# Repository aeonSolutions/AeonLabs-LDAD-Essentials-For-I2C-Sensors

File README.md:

[Main Catalogue](https://github.com/aeonSolutions/PCB-Prototyping-Catalogue) >> 
[Construction Industry](https://github.com/aeonSolutions/PCB-Prototyping-Catalogue/tree/main/Construction%20Industry)  >>  Smart Technologies for Building Smart Network Connectivity

<p align="right">
 <a href="https://github-com.translate.goog/aeonSolutions/PCB-Prototyping-Catalogue/tree/main?_x_tr_sl=en&_x_tr_tl=pt&_x_tr_hl=en&_x_tr_pto=wapp">Change Language</a> <br>
Last update: 01-12-2023
</p>

# AeonLabs LDAD Essentials For I2C Sensors
This repo contains the KiCad files for the LDAD Essentials features up to  6 I2C sensor connections has WIFI and BLE connectivity and is powered by a 4.2v Lipo Battery.
This PCB was made to Fit a [Legrand Aftakdoos Leeq](https://www.google.com/search?q=Legrand+Aftakdoos+leeq&newwindow=1&client=opera&sxsrf=APq-WBudoCNXlyJkT8RVjwlvQol-xiGYpA%3A1650729585719&ei=cSJkYqmqK_GAi-gPo-ey4AQ&ved=0ahUKEwjpps70xqr3AhVxwAIHHaOzDEwQ4dUDCA0&uact=5&oq=Legrand+Aftakdoos+leeq&gs_lcp=Cgdnd3Mtd2l6EAMyBQghEKABMgUIIRCgATIFCCEQoAE6BwgAEEcQsAM6BggAEBYQHkoECEEYAEoECEYYAFDhBViiD2DMEGgBcAF4AIABpgGIAfkDkgEDMC40mAEAoAEByAEIwAEB&sclient=gws-wiz) 89x43mm waterproof enclosure.

*Don't forget to LIKE , SHARE and subscribe the free whatsApp group* and if you liked this PCB consider buying me a cup of coffee. Links below.

### Status
  revision 1.0 tested and working

If you already tested this PCB send me a message. Thank you

## Revisions
- revision 1.0
  
## Download options
Download this repository if you need the KiCad Files or, download the Gerber files in the release section of this repository

## Liked it ? Get a Free PCB for yourself
Send me your Device or hardware and i will design a custom PCB for it. Free of charge. Contact-me on WhatsApp or email for more info. 

## Q&A WhatsApp Group
If you have any Questions or simply  like this kind of projects and want to stay updated with the latest research ideas and prototypes during the day and week, join the WhatsApp Group
[A.I. Things](https://chat.whatsapp.com/FkNC7u83kuy2QRA5sqjBVg)

## Fully assembled PCB
Alternatively, and if you do not want to build a PCB by yourself and like to buy one:

The price starts at 30eur plus postage fees.
(I will also deliver the assembled PCB with all the components in place at a fair aditonal cost).

#### Be supportive of my dedication and work towards technology education and buy me a coffee. Link below.

## PCB Parts list
- DC2DC converter HX4002B x2 : https://s.click.aliexpress.com/e/_Ak7IPx
- Capacitor 100nF SMD 1206 : https://s.click.aliexpress.com/e/_AVdmzr
- Capacitor 2.2uF SMD 1206 : https://s.click.aliexpress.com/e/_AVdmzr
- Resistor SMD 1206 330R x3 : https://s.click.aliexpress.com/e/_A7OXrR
- ESP32 WROOM32 x1 : https://s.click.aliexpress.com/e/_AF7N6l
- KF350 Screw pitch 3.5mm Straight 3 Pin pcb terminal block : https://s.click.aliexpress.com/e/_AChDnp

- This PCB connects with the any I2C compatible sensor such as the SHT3x, SG30, etc :  https://s.click.aliexpress.com/e/_A1piJN

## PCB Enclosure
The enclosure for this PCB can be bought online by searching for "[Legrand Aftakdoos Leeq](https://www.google.com/search?q=Legrand+Aftakdoos+leeq&newwindow=1&client=opera&sxsrf=APq-WBudoCNXlyJkT8RVjwlvQol-xiGYpA%3A1650729585719&ei=cSJkYqmqK_GAi-gPo-ey4AQ&ved=0ahUKEwjpps70xqr3AhVxwAIHHaOzDEwQ4dUDCA0&uact=5&oq=Legrand+Aftakdoos+leeq&gs_lcp=Cgdnd3Mtd2l6EAMyBQghEKABMgUIIRCgATIFCCEQoAE6BwgAEEcQsAM6BggAEBYQHkoECEEYAEoECEYYAFDhBViiD2DMEGgBcAF4AIABpgGIAfkDkgEDMC40mAEAoAEByAEIwAEB&sclient=gws-wiz)".

## Firmware Download 
one can use the PCB in the repository [AeonLabs-MCU-Burner-USB-to-UART-TTL](https://github.com/aeonSolutions/AeonLabs-MCU-Burner-USB-to-UART-TTL) to program the ESP32 WROOM32 MCU on this PCB.

## Author

You can get in touch with me on my LinkedIn Profile:

#### Miguel Tomas

You can also follow my GitHub Profile to stay updated about my latest projects: 

<br>

### Be supportive of my dedication and work towards technology education and buy me a cup of coffee
The PCB Desgin Files i provide here for anyone to use are free. If you like this Smart Device or use it, please consider buying me a cup of coffee, a slice of pizza or a book to help me study, eat and think new PCB design files.

<br />

### Make a donation on Paypal
Make a donation on paypal and get a TAX refund*.

<br>

### Support all these open hardware projects and become a patreon  
Liked any of my PCB KiCad Designs? Help and Support my open work to all by becomming a LDAD Patreon.
In return I will give a free PCB design in KiCad to all patreon supporters. To learn more go to patreon.com. Link below.

#

### License

Before proceeding to download any of AeonLabs software solutions for open-source development and/or PCB hardware electronics solutions for open-hardware development make sure you are choosing the right license for your project. See [AeonLabs Solutions for Open Hardware & Source Development](https://github.com/aeonSolutions/PCB-Prototyping-Catalogue/wiki/AeonLabs-Solutions-for-Open-Hardware-&-Source-Development) for more information.

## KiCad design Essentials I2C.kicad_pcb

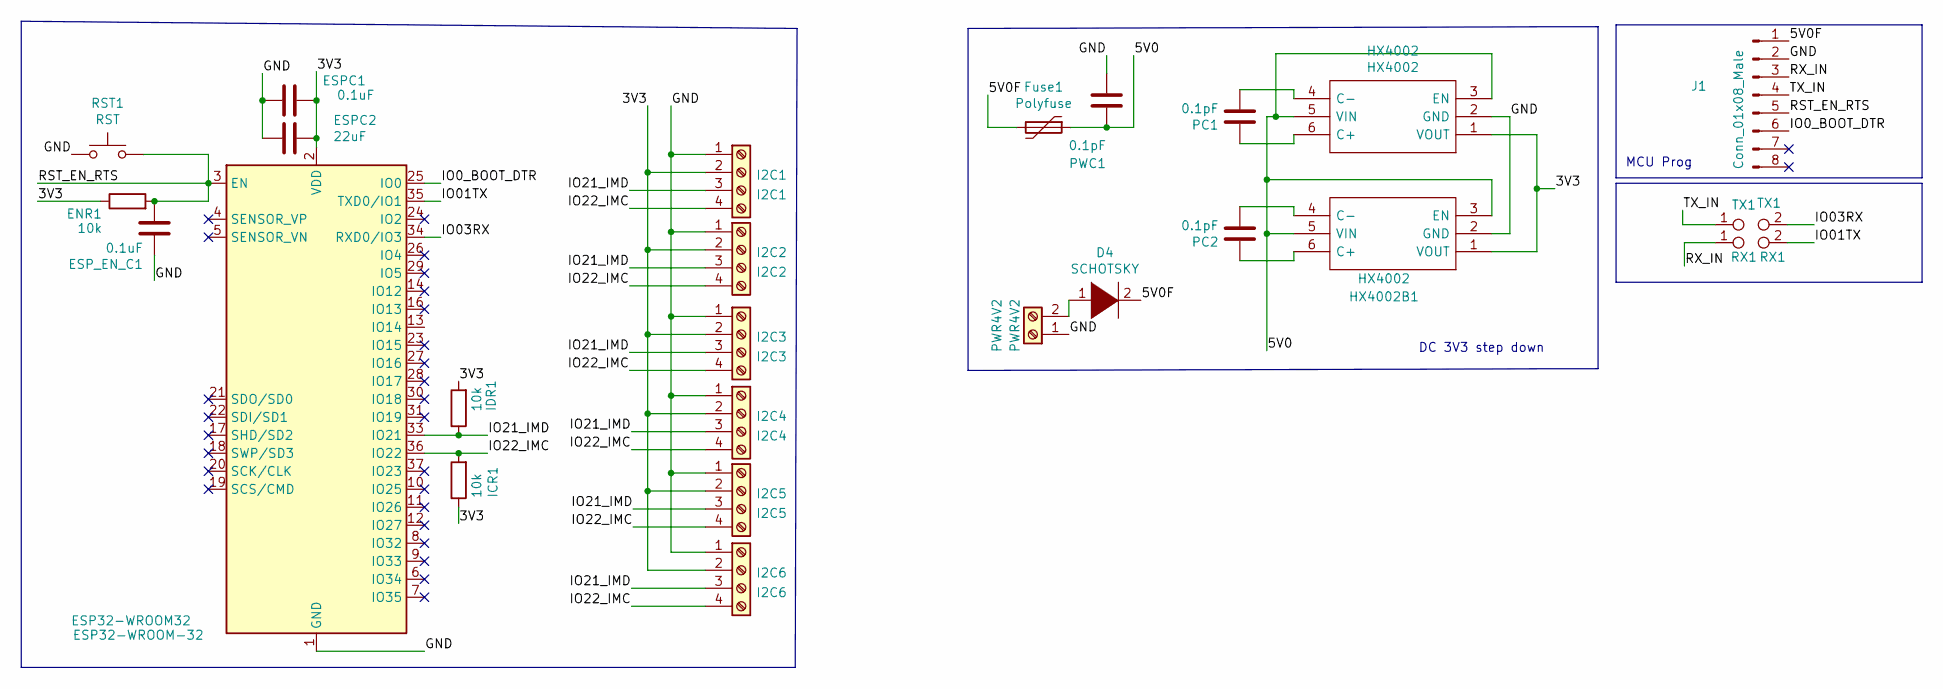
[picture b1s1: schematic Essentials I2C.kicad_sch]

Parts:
D4: SCHOTSKY; D_1210_3225Metric_Pad1.42x2.65mm_HandSolder
ENR1: 10k; R_1206_3216Metric_Pad1.30x1.75mm_HandSolder
ESP32-WROOM32: ESP32-WROOM-32
ESPC1: 0.1uF; C_1206_3216Metric_Pad1.33x1.80mm_HandSolder
ESPC2: 22uF; C_1206_3216Metric_Pad1.33x1.80mm_HandSolder
ESP_EN_C1: 0.1uF; C_1206_3216Metric_Pad1.33x1.80mm_HandSolder
Fuse1: Polyfuse; Fuse_1206_3216Metric_Pad1.42x1.75mm_HandSolder
HX4002, HX4002B1: HX4002; HX4002 SOT95 P280X125-6N; Manufacturer_Part_Number HX4002
I2C1: I2C1; TerminalBlock_4Ucon_1x04_P3.50mm_Vertical
I2C2: I2C2; TerminalBlock_4Ucon_1x04_P3.50mm_Vertical
I2C3: I2C3; TerminalBlock_4Ucon_1x04_P3.50mm_Vertical
I2C4: I2C4; TerminalBlock_4Ucon_1x04_P3.50mm_Vertical
I2C5: I2C5; TerminalBlock_4Ucon_1x04_P3.50mm_Vertical
I2C6: I2C6; TerminalBlock_4Ucon_1x04_P3.50mm_Vertical
ICR1: 10k; R_True_1206_3216Metric
IDR1: 10k; R_True_1206_3216Metric
J1: Conn_01x08_Male; SOIC_clipProgSmall
PC1, PC2: 0.1pF; C_1206_3216Metric_Pad1.33x1.80mm_HandSolder
PWC1: 0.1pF; C_1206_3216Metric_Pad1.33x1.80mm_HandSolder
PWR4V2: PWR4V2; JST_EH_S2B-EH_1x02_P2.50mm_Horizontal
RST1: RST; SW_Push_SPST_NO_Alps_SKRK AliExpress
RX1: RX1; TestPoint_Pad_Bridge_1.0x1.0mm
TX1: TX1; TestPoint_Pad_Bridge_1.0x1.0mm

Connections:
/3V3: ENR1.1, ESP32-WROOM32.2 (VDD), ESPC1.1, ESPC2.1, HX4002.1 (VOUT), HX4002B1.1 (VOUT), I2C1.2, I2C2.2, I2C3.2, I2C4.2, I2C5.2, I2C6.2, ICR1.1, IDR1.2
/5V0: Fuse1.1, HX4002.3 (EN), HX4002.5 (VIN), HX4002B1.3 (EN), HX4002B1.5 (VIN), PWC1.1
/5V0F: D4.2 (A), Fuse1.2, J1.1
/GND: ESP32-WROOM32.1 (GND), ESP32-WROOM32.15 (GND), ESP32-WROOM32.38 (GND), ESP32-WROOM32.39 (GND), ESPC1.2, ESPC2.2, ESP_EN_C1.1, HX4002.2 (GND), HX4002B1.2 (GND), I2C1.1, I2C2.1, I2C3.1, I2C4.1, I2C5.1, I2C6.1, J1.2, PWC1.2, PWR4V2.1, RST1.1
/IO0_BOOT_DTR: ESP32-WROOM32.25 (IO0), J1.6
/IO01TX: ESP32-WROOM32.35 (TXD0/IO1), RX1.2
/IO03RX: ESP32-WROOM32.34 (RXD0/IO3), TX1.2
/IO21_IMD: ESP32-WROOM32.33 (IO21), I2C1.3, I2C2.3, I2C3.3, I2C4.3, I2C5.3, I2C6.3, IDR1.1
/IO22_IMC: ESP32-WROOM32.36 (IO22), I2C1.4, I2C2.4, I2C3.4, I2C4.4, I2C5.4, I2C6.4, ICR1.2
/RST_EN_RTS: ENR1.2, ESP32-WROOM32.3 (EN), ESP_EN_C1.2, J1.5, RST1.2
/RX_IN: J1.3, RX1.1
/TX_IN: J1.4, TX1.1
unnamed: D4.1 (K), PWR4V2.2
unnamed: HX4002.4 (C-), PC1.2
unnamed: HX4002.6 (C+), PC1.1
unnamed: HX4002B1.4 (C-), PC2.2
unnamed: HX4002B1.6 (C+), PC2.1

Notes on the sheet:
DC 3V3 step down
MCU Prog

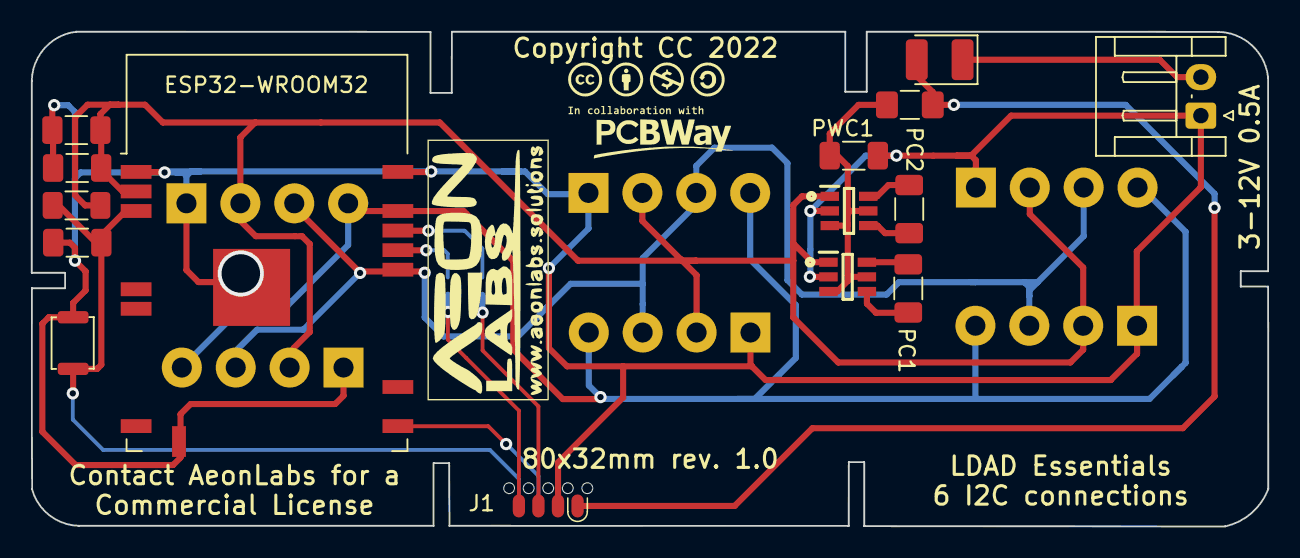
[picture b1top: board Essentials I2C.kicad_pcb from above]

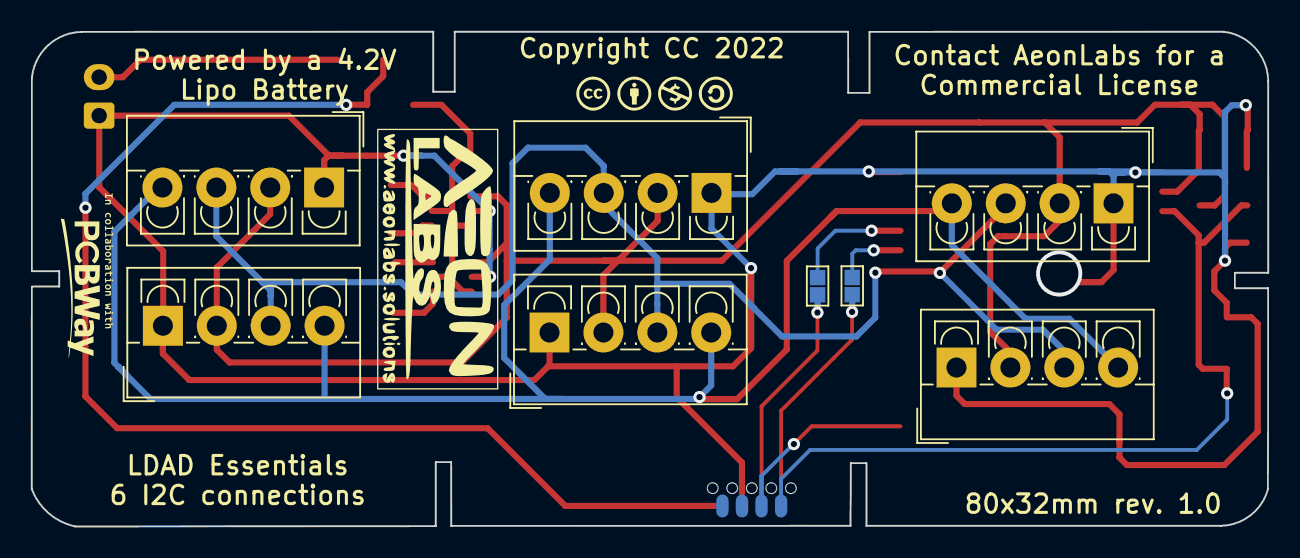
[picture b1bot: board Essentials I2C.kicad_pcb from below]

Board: 2 copper layers, 80.3 x 32.1 mm, 23 parts (8 on the bottom side), 17 nets.

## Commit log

2022-04-24 rev. 1.0

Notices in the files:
Essentials I2C.kicad_pcb:
Copyright CC 2022
